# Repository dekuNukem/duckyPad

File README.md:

# duckyPad: Do-It-All Mechanical Macropad

[Get duckyPad](https://dekunukem.github.io/duckyPad-Pro/doc/landing.html) | [Official Discord](https://discord.gg/4sJCBx5) | [Getting Started](getting_started.md) | [Table of Contents](#table-of-contents)

----

duckyPad is a 15-key **mechanical macropad** for power users who demand **advanced macro scripting and customisation** beyond the shackles of QMK/VIA.

Using a [turing-complete scripting language](https://dekunukem.github.io/duckyPad-Pro/doc/duckyscript_info.html), you can automate **any keyboard/mouse input** you want, from **simple combos** to **full-blown programs**.

## Get One

duckyPad was successfully [funded on Kickstarter](https://www.kickstarter.com/projects/dekunukem/duckypad-do-it-all-mechanical-macropad) thanks to the [amazing backers!](kickstarter_backers.md)

* Now Available [on my Tindie Store](https://www.tindie.com/products/dekunukem/duckypad-do-it-all-mechanical-macropad/)

## Highlights

duckyPad has all the basics:

* **Hot-swap**
* Per-key RGB
* Fully **open-source**

But also unique features **not seen anywhere else**:

* Custom **[duckyScript](https://dekunukem.github.io/duckyPad-Pro/doc/duckyscript_info.html)** engine, **NOT QMK/VIA**.
* **Longer and more complex** macros
* **OLED** screen
* **32 profiles** of 15 keys, 480 macros total.
* [Automatic profile switching](https://github.com/dekuNukem/duckyPad-profile-autoswitcher) based on active window.
* microSD storage, move between devices with ease.
* No proprietary drivers, works out-of-box.

## duckyScript vs QMK/VIA

duckyPad uses **duckyScript**, originally designed for [USB Rubber Ducky](https://shop.hak5.org/products/usb-rubber-ducky-deluxe).

Compared to QMK/VIA, you get:

* **Much Longer Macros**
	* [Entire Bee Movie](resources/beemovie.txt) in one macro? Yes please!
	* Up to 480 macros

* **Turing-Complete Scripting**
	* Variables, conditions, loops, functions, and more.
	* Executed on [32-bit Bytecode VM](https://duckypad.github.io/DuckStack/)
	* With **Scratch** and **Non-volatile Memory**

* **Advanced Interactions**
	* Reading Buttons
	* Print to OLED screen
	* Change RGB Color

* **SD Card Storage**
	* Fast Configuration / Backup / Deployment
	* No sketchy drivers or apps
	* No recompiling

While QMK/VIA are great for regular keyboards, they are rather limited at input automations.

duckyScript is a no-brainer for **power users** with more demanding scripting needs.

## 🆕 duckyPad Pro

duckyPad Pro is an updated model with:

* Rotary Encoders
* More Keys
* Bluetooth
* Bigger Display
* More Script Storage
* Expansion Module

👉👉👉 [Purchase Link](https://www.tindie.com/products/37399/) | [More Info](https://dekunukem.github.io/duckyPad-Pro/)

## Discord Community

Feel free to join our [Official Discord](https://discord.gg/4sJCBx5) for discussions, questions, sharing scripts, and latest updates!

## How It Works / Showcase

* Create up to **32 profiles**, one for each application.

* Assign up to **15 keys** per profile

* Names are shown on OLED screen

* Write a **duckyScript** for each key

### Easy Start

* **duckyScript** is a language for automating inputs

	* At simplest, you just tell it **what key to press!**

* Such as **key combos** of your favorite app

`CTRL a` , `CTRL +`, etc.

### Up a Notch

* Once familiar, you can write **longer multi-line macros** to further speed up everyday task.

* Such as **filling forms** and typing **boilerplate text** with one keypress.

```
STRING Michael Scott
TAB
STRING United States
ENTER
STRING 5705550100
TAB
STRING michael.scott@dundermifflin.com
TAB
```

Or a simple mouse jiggler:

```
WHILE TRUE
	MOUSE_MOVE $_RANDOM_INT $_RANDOM_INT
	DELAY 100
END_WHILE
```

### Full Potential

* Going all-out, duckyScript is a **Turing-Complete** **general-purpose** language.
* You can use it to:
	* Read Buttons
	* Write to OLED screen
	* Change RGB colors
	* Perform operations with **32-bit variables**, **conditions**, **loops**, **function call**s, and more!
* Write ultra-specific macros for your exact needs

```
RGB_SET 1 128 0 255

OLED_PRINT You are in a maze
OLED_PRINT of twisty little passages

VAR choice = _READKEY

IF choice == 1
    OLED_CURSOR 0 10
    OLED_PRINT It is a dead end.
    OLED_PRINT Something moves
    OLED_PRINT behind you.
END_IF
```

### Hackerman

* Of course, by automating HID inputs, you can take over an entire computer with the push of a button!

* This is known as [BadUSB attack](https://arstechnica.com/information-technology/2014/07/this-thumbdrive-hacks-computers-badusb-exploit-makes-devices-turn-evil/), and was the original purpose of [USB Rubber Ducky](https://shop.hak5.org/products/usb-rubber-ducky-deluxe).

---------

### Nothing Like It

* From **simple shortcuts** to **full-blown programs**, duckyScript can easily achieve what was impossible on QMK/VIA.

* Each macro can contain over **50,000 characters**

* Store **480 macros** in total

* Executed on custom [virtual stack machine](https://duckypad.github.io/DuckStack/)

## Features

### Switches & Keycaps

duckyPad is compatible with Cherry MX-style mechanical switches (3 or 5-pin).

By default, duckyPad comes with blank translucent ABS R4 keycaps:

You can use your own as well.

### Hot-swap Sockets

duckyPad supports hot-swapping with Kailh sockets.

You can install/remove the switches by hand, **`no soldering needed`**.

### Per-key RGB backlight

Each key on duckyPad has its own RGB backlight. User-configurable colour & brightness.

### OLED screen

duckyPad has an OLED screen. It displays current **`profile and key names`**, so you know what each key does at a glance.

* 128x128
* 1.3 inch
* High contrast with true black
* Burn-in Prevention

### Companion App

[Use the open-source configurator](https://github.com/duckyPad/duckyPad-Configurator) to set up your duckyPad Pro.

* Windows | Mac | Linux
* No account / subscription needed
* No data collection / telemetry

## Profile Auto-switching

* [Automatically jump to the appropriate profile](https://github.com/dekuNukem/duckyPad-profile-autoswitcher)
* Based on **current active window**

### USB-C and Device Compatibility

duckyPad uses USB-C connector for maximum device compatibility.

You can use duckyPad out-of-box on pretty much anything that supports USB keyboards, **`no driver needed`**. Examples include:

* PC
* Mac
* Linux
* Raspberry Pi
* iPhone / iPad
* Android phones and tablets
* Chromebooks
* Game consoles

duckyPad’s firmware can also be [easily updated via USB-C](firmware_updates_and_version_history.md) for new features and bug fixes.

### Keyboard Layouts

duckyPad supports multiple keyboard layouts:

* English (US)
* English (UK)
* French
* Belgium
* German
* Dvorak
* ...and more [user-created](keymap_instructions.md) layouts!

### Dimensions

[Click me](pcb/plates) for vector files of front and back plates.

[Click me](resources/pics/dimensions.png) for dimensions drawings.

## Getting Started

Please see [the instruction manual](./getting_started.md) on how to use your duckyPad.

## I Want One!

duckyPad is [now available on Tindie.](https://www.tindie.com/products/21984)

Also consider [joining our discord](https://discord.gg/4sJCBx5) for latest updates and discussions.

## Table of Contents

[Main page](README.md)

[Getting Started Guide](getting_started.md)

[Kit Assembly Guide](kit_assembly_guide.md)

[Using duckyScript](https://dekunukem.github.io/duckyPad-Pro/doc/duckyscript_info.html)

[Common issues / Troubleshooting](troubleshooting.md)

[Firmware Updates and Version History](firmware_updates_and_version_history.md)

[Make Your Own Keymap](./keymap_instructions.md)

[Build a duckyPad Yourself](build_it_yourself.md)

[Kickstarter Backer Acknowledgments](kickstarter_backers.md)

## Questions or Comments?

Please feel free to [open an issue](https://github.com/dekuNukem/duckypad/issues), ask in the [official duckyPad discord](https://discord.gg/4sJCBx5), DM me on discord `dekuNukem#6998`, or email `dekuNukem`@`gmail`.`com` for inquires.

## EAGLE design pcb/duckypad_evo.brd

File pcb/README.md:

Currently no pcb files are available.

The used pins can be seen from the lul.ioc files when the device is handsoldered.

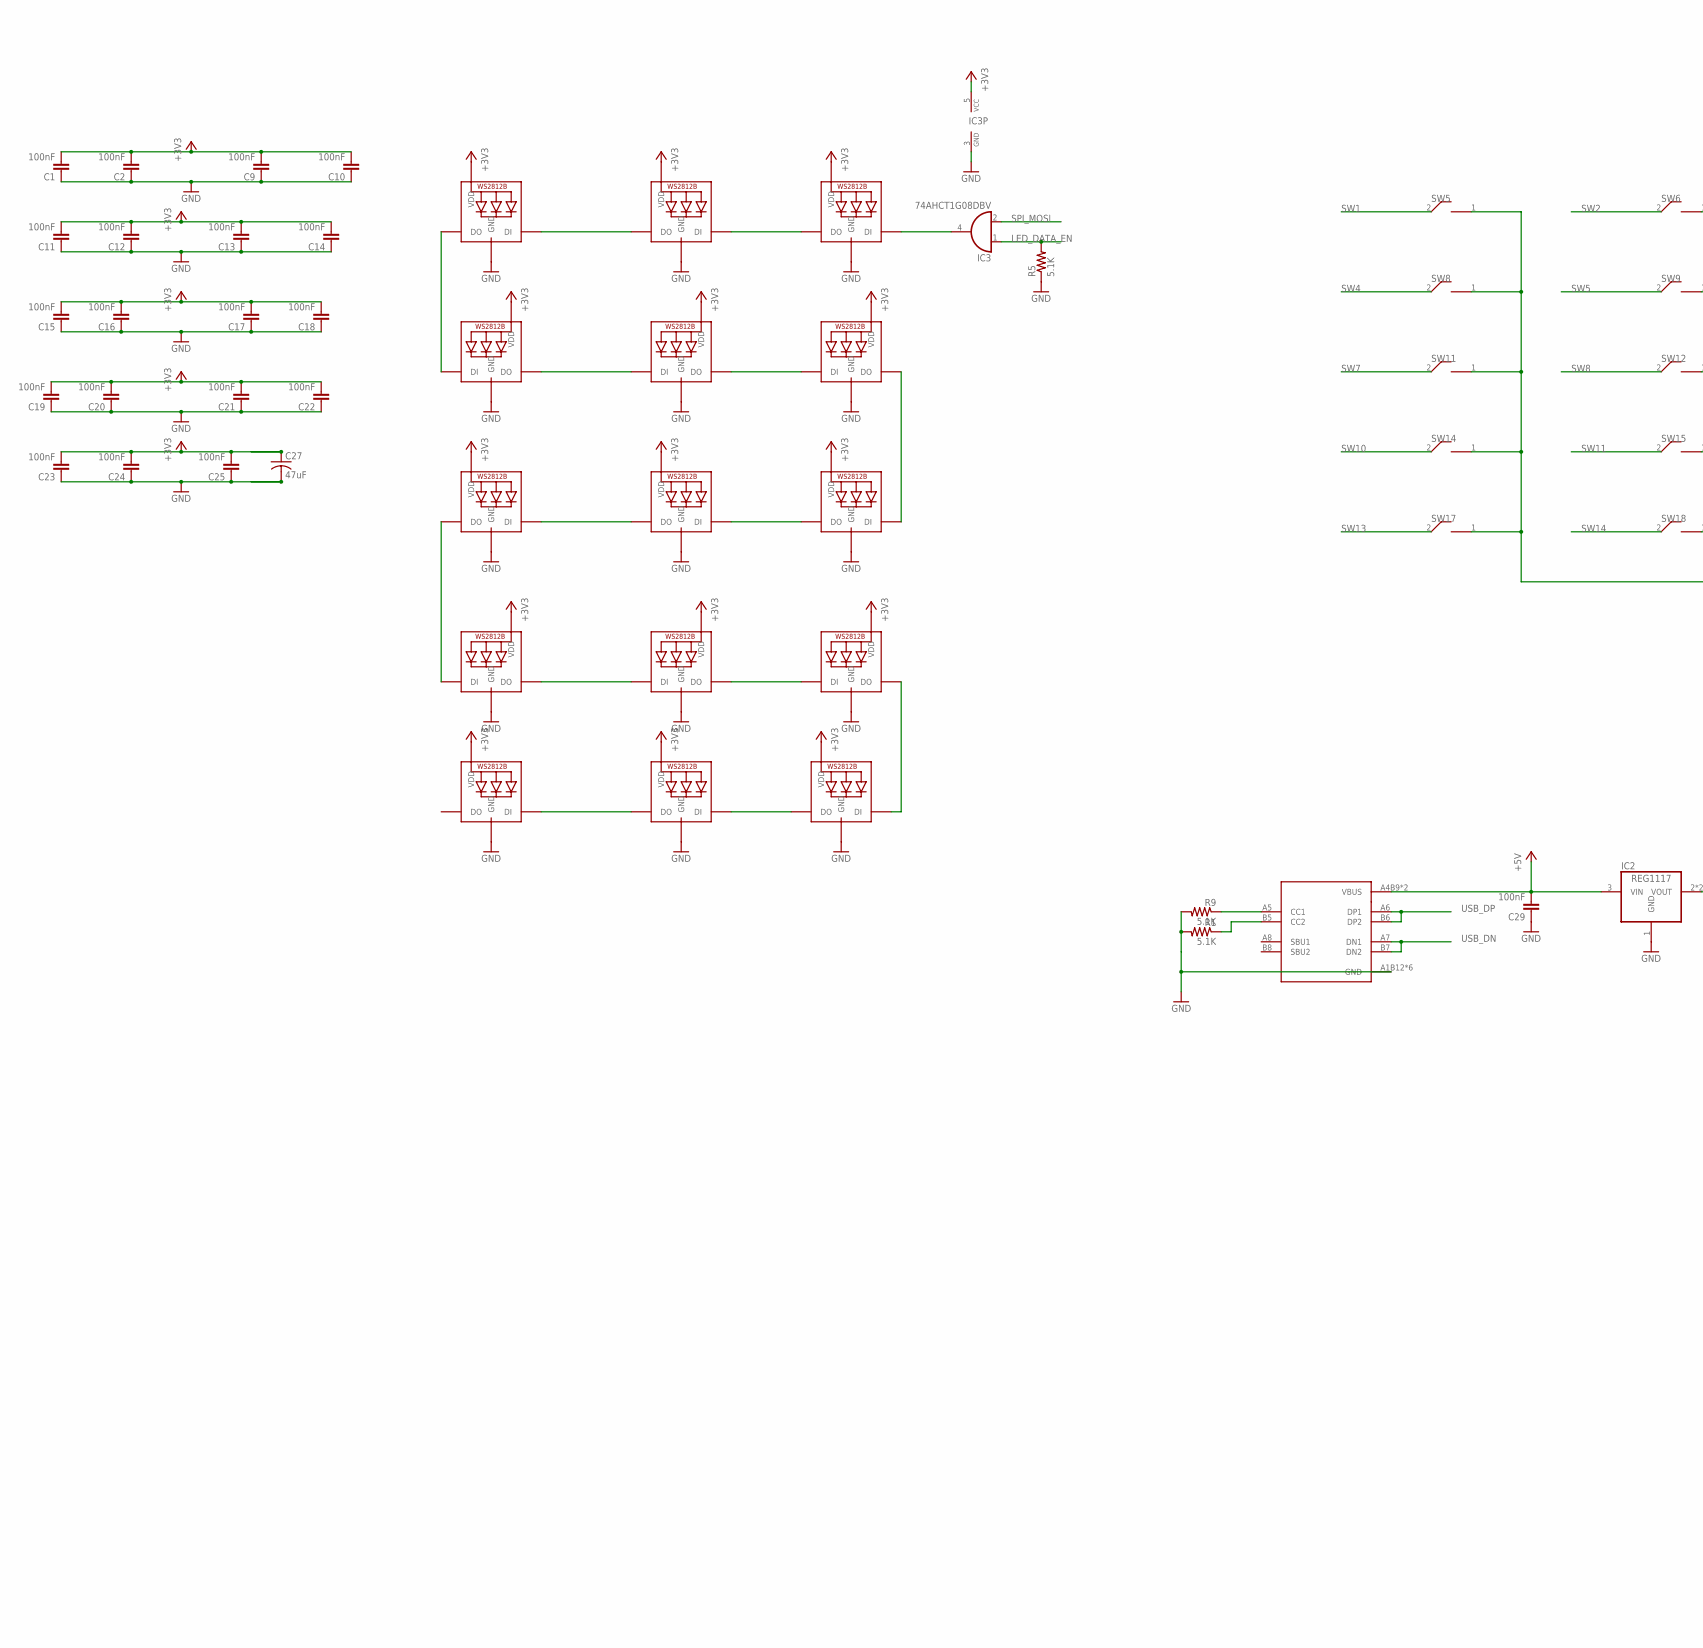
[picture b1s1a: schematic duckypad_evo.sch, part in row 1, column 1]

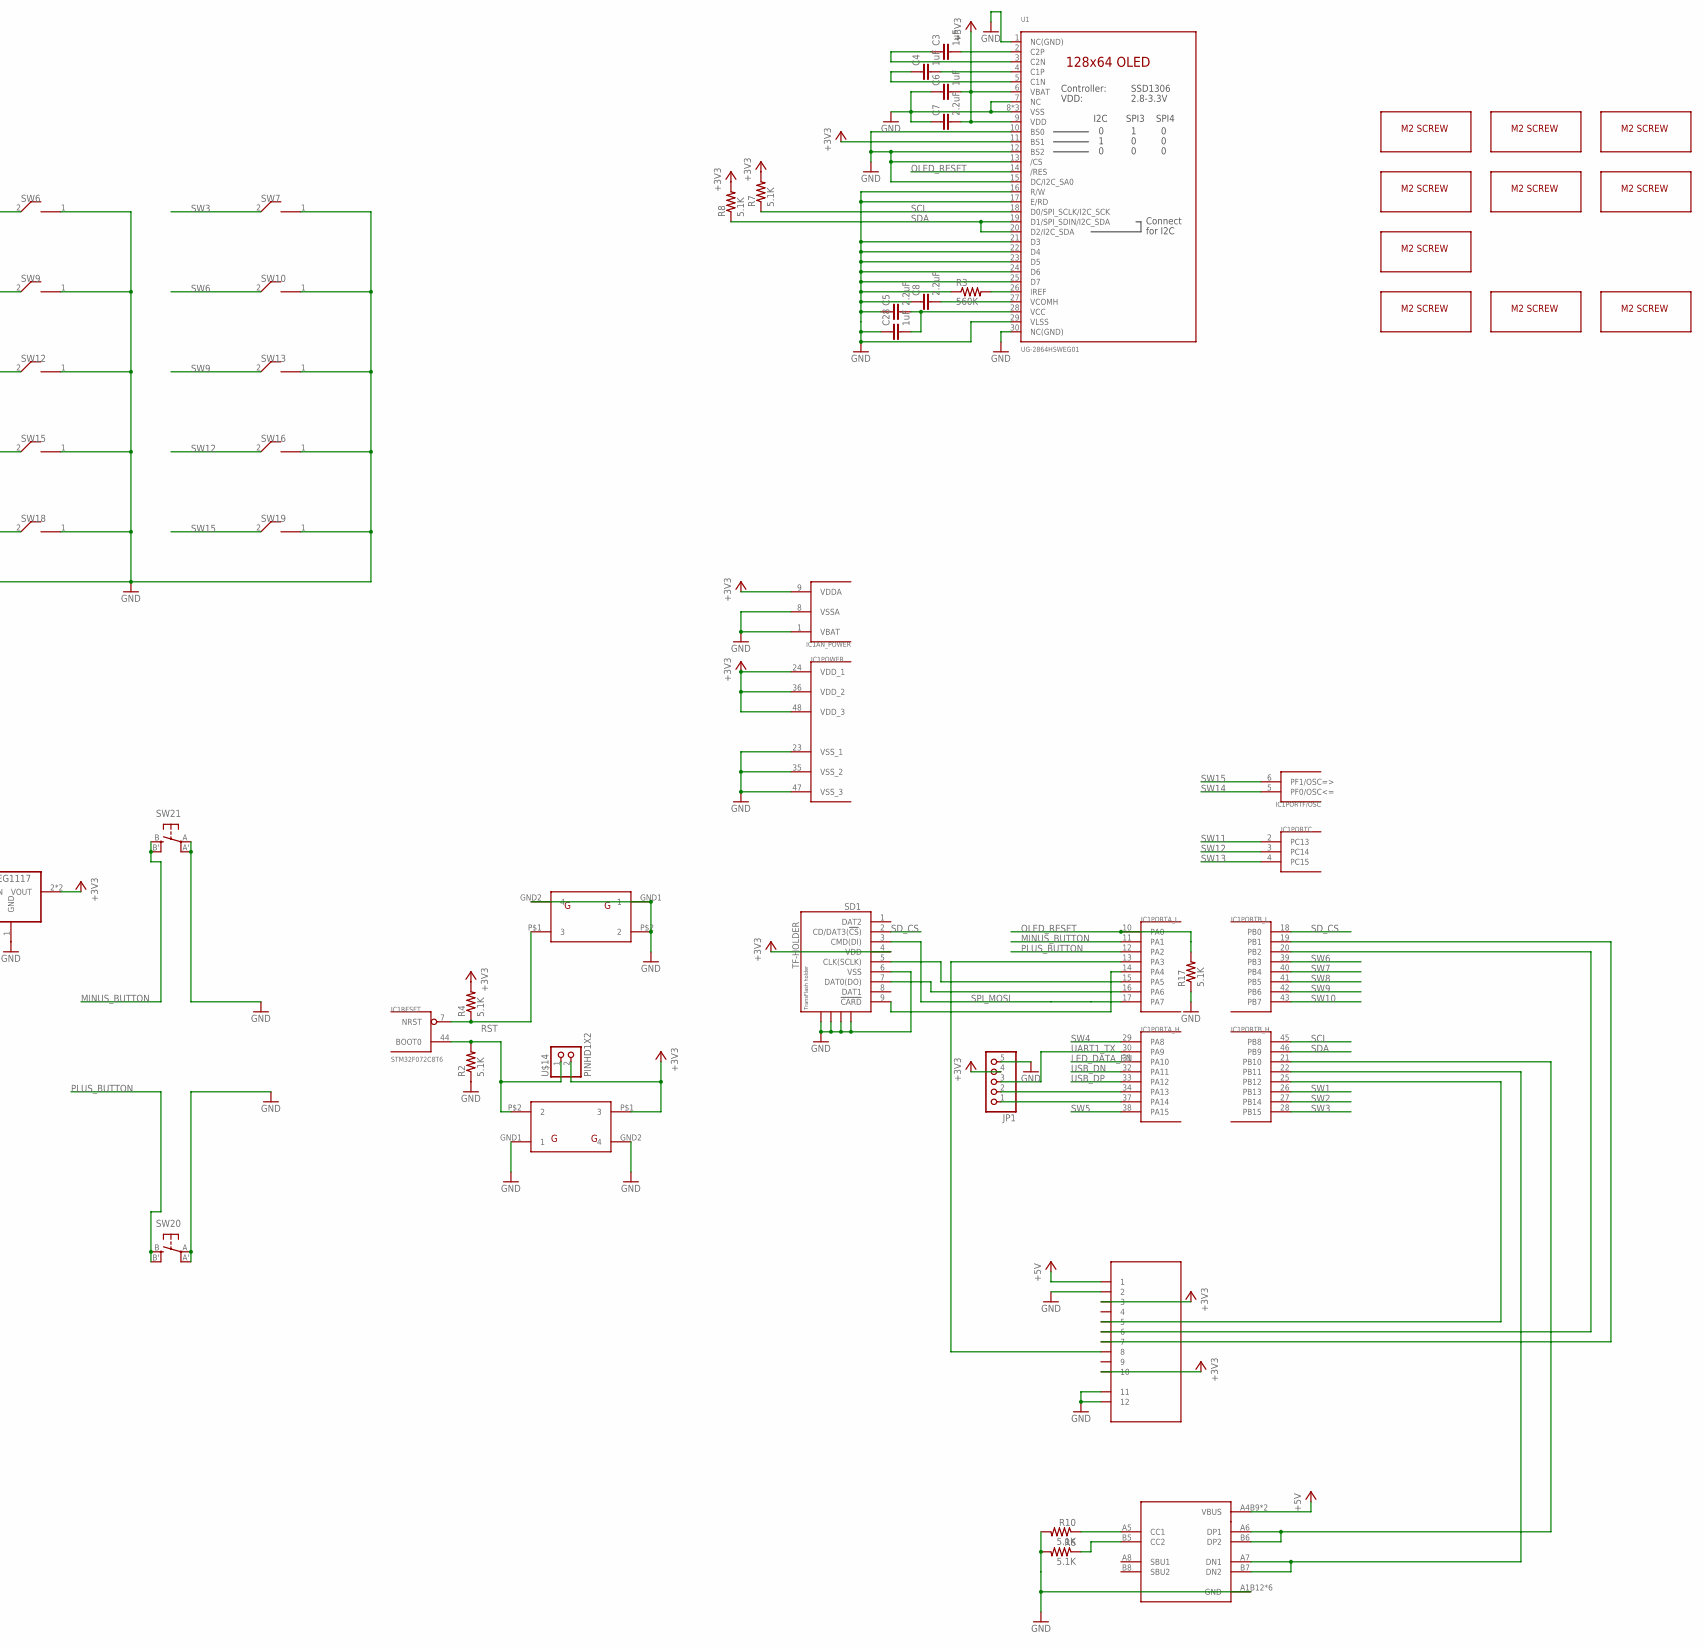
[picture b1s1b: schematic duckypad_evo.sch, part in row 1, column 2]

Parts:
C1, C2, C9, C10, C11, C12, C13, C14, C15, C16, C17, C18, C19, C20, C21, C22, C23, C24, C25, C29: 100nF; 0805@1
C3, C4, C6, C28: 1uF; 0805@1
C5, C7, C8: 2.2uF; 0805@1
C27: 47uF; C1210
IC1: STM32F072C8T6; TQFP48
IC2: REG1117; SOT223
IC3: 74AHCT1G08DBV; SOT23-5
JP1: PINHD-1X5; 1X05
LED1, LED2, LED3, LED4, LED5, LED6, LED7, LED8, LED9, LED10, LED11, LED12, LED13, LED14, LED15: WS2812B; REVERSE_MNT
R1, R2, R4, R5, R6, R7, R8, R9, R10, R17: 5.1K; 0805
R3: 560K; 0805
SD1: TF-HOLDER; TF-PULL
SH1: SH10P; DUCKYPAD_SM12B-SSR-H-TB
SW3, SW4: 3POS_SLIDE_SWITCH_324_SW; SIDEPUSH
SW5, SW6, SW7, SW8, SW9, SW10, SW11, SW12, SW13, SW14, SW15, SW16, SW17, SW18, SW19: KAILH_SWITCH_SOCKET_KAILH_SWITCH_SOCKET; KAILH_SWITCH_SOCKET_SWITCH_SOCKET
SW20, SW21: SPST_TACT-EVQQ2; EVQ-Q2
U1: UG-2864HSWEG01; LUL_UG-2864HSWEG01_1.3_WRAPAROUND
U2, U3: USBC_16P; USBC_16P_FOOT
U$7, U$8, U$9, U$10, U$11, U$12, U$13, U$15, U$16, U$23: M2_SCREW_DEV; M2_SCREW_FOOT
U$14: PINHD1X2; 1X02

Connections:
+3V3: C1.2, C2.2, C6.2, C7.2, C9.2, C10.2, C11.2, C12.2, C13.2, C14.2, C15.2, C16.2, C17.2, C18.2, C19.2, C20.2, C21.2, C22.2, C23.2, C24.2, C25.2, C27.1, IC1.9 (VDDA), IC1.24 (VDD_1), IC1.36 (VDD_2), IC1.48 (VDD_3), IC2.2 (VOUT), IC2.4 (VOUT), IC3.5 (VCC), JP1.4, LED1.VDD, LED2.VDD, LED3.VDD, LED4.VDD, LED5.VDD, LED6.VDD, LED7.VDD, LED8.VDD, LED9.VDD, LED10.VDD, LED11.VDD, LED12.VDD, LED13.VDD, LED14.VDD, LED15.VDD, R4.2, R7.2, R8.2, SD1.4 (VDD), SH1.3, SH1.10, SW4.P$1 (3), U1.6 (VBAT), U1.9 (VDD), U1.11 (BS1), U$14.2
+5V: C29.2, IC2.3 (VIN), SH1.1, U2.A4B9 (VBUS), U2.B4A9 (VBUS), U3.A4B9 (VBUS), U3.B4A9 (VBUS)
BUTTON_DEBUG: IC1.44 (BOOT0), R2.2, SW4.P$2 (2), U$14.1
GND: C1.1, C2.1, C5.1, C6.1, C7.1, C8.1, C9.1, C10.1, C11.1, C12.1, C13.1, C14.1, C15.1, C16.1, C17.1, C18.1, C19.1, C20.1, C21.1, C22.1, C23.1, C24.1, C25.1, C27.2, C28.1, C29.1, IC1.1 (VBAT), IC1.8 (VSSA), IC1.23 (VSS_1), IC1.35 (VSS_2), IC1.47 (VSS_3), IC2.1 (GND), IC3.3 (GND), JP1.5, LED1.GND, LED2.GND, LED3.GND, LED4.GND, LED5.GND, LED6.GND, LED7.GND, LED8.GND, LED9.GND, LED10.GND, LED11.GND, LED12.GND, LED13.GND, LED14.GND, LED15.GND, R1.2, R2.1, R3.1, R5.1, R6.2, R9.2, R10.2, R17.1, SD1.6 (VSS), SD1.S1, SD1.S2, SD1.S3, SD1.S4, SH1.2, SH1.FIT@1 (11), SH1.FIT@2 (12), SW3.GND1 (1), SW3.GND2 (4), SW3.P$2 (2), SW4.GND1 (1), SW4.GND2 (4), SW5.1 (2), SW6.1 (2), SW7.1 (2), SW8.1 (2), SW9.1 (2), SW10.1 (2), SW11.1 (2), SW12.1 (2), SW13.1 (2), SW14.1 (2), SW15.1 (2), SW16.1 (2), SW17.1 (2), SW18.1 (2), SW19.1 (2), SW20.A, SW20.A' (P1), SW21.A, SW21.A' (P1), U1.1 (NC(GND)), U1.7 (NC), U1.8 (VSS), U1.10 (BS0), U1.12 (BS2), U1.13 (/CS), U1.15 (DC/I2C_SA0), U1.16 (R/W), U1.17 (E/RD), U1.21 (D3), U1.22 (D4), U1.23 (D5), U1.24 (D6), U1.25 (D7), U1.29 (VLSS), U1.30 (NC(GND)), U1.31 (VSS), U1.32 (VSS), U2.A1B12 (GND), U2.B11A12 (GND), U2.P$13 (GND), U2.P$14 (GND), U2.P$15 (GND), U2.P$16 (GND), U3.A1B12 (GND), U3.B11A12 (GND), U3.P$13 (GND), U3.P$14 (GND), U3.P$15 (GND), U3.P$16 (GND)
LED_DATA_EN: IC1.31 (PA10), IC3.1 (I0), R5.2
MINUS_BUTTON: IC1.11 (PA1), SW21.B (S), SW21.B' (S1)
unnamed: R6.1, U3.B5 (CC2)
unnamed: IC1.20 (PB2), SH1.6
unnamed: R3.2, U1.26 (IREF)
unnamed: C3.2, U1.2 (C2P)
unnamed: C3.1, U1.3 (C2N)
unnamed: C4.2, U1.4 (C1P)
unnamed: C4.1, U1.5 (C1N)
unnamed: IC1.15 (PA5), SD1.5 (CLK(SCLK))
unnamed: LED2.DIN (DI), LED3.DOUT (DO)
unnamed: IC1.16 (PA6), SD1.7 (DAT0(DO))
unnamed: C5.2, C28.2, U1.28 (VCC)
unnamed: C8.2, U1.27 (VCOMH)
unnamed: IC1.19 (PB1), SH1.7
unnamed: IC1.14 (PA4), SD1.9 (!CARD)
unnamed: LED1.DIN (DI), LED2.DOUT (DO)
unnamed: IC1.22 (PB11), U3.A7 (DN1), U3.B7 (DN2)
unnamed: LED1.DOUT (DO), LED4.DIN (DI)
unnamed: LED4.DOUT (DO), LED5.DIN (DI)
unnamed: LED5.DOUT (DO), LED6.DIN (DI)
unnamed: LED6.DOUT (DO), LED9.DIN (DI)
unnamed: LED8.DIN (DI), LED9.DOUT (DO)
unnamed: LED7.DIN (DI), LED8.DOUT (DO)
unnamed: LED7.DOUT (DO), LED10.DIN (DI)
unnamed: LED10.DOUT (DO), LED11.DIN (DI)
unnamed: LED11.DOUT (DO), LED12.DIN (DI)
unnamed: LED12.DOUT (DO), LED15.DIN (DI)
unnamed: LED14.DIN (DI), LED15.DOUT (DO)
unnamed: LED13.DIN (DI), LED14.DOUT (DO)
unnamed: IC3.4 (O), LED3.DIN (DI)
unnamed: IC1.21 (PB10), U3.A6 (DP1), U3.B6 (DP2)
unnamed: R1.1, U2.B5 (CC2)
unnamed: IC1.37 (PA14), JP1.1
unnamed: R9.1, U2.A5 (CC1)
unnamed: IC1.34 (PA13), JP1.2
unnamed: IC1.25 (PB12), SH1.5
unnamed: R10.1, U3.A5 (CC1)
unnamed: IC1.13 (PA3), SH1.8
OLED_RESET: IC1.10 (PA0), R17.2, U1.14 (/RES)
PLUS_BUTTON: IC1.12 (PA2), SW20.B (S), SW20.B' (S1)
RST: IC1.7 (NRST), R4.1, SW3.P$1 (3)
SCL: IC1.45 (PB8), R7.1, U1.18 (D0/SPI_SCLK/I2C_SCK)
SDA: IC1.46 (PB9), R8.1, U1.19 (D1/SPI_SDIN/I2C_SDA), U1.20 (D2/I2C_SDA)
SD_CS: IC1.18 (PB0), SD1.2 (CD/DAT3(!CS!))
SPI_MOSI: IC1.17 (PA7), IC3.2 (I1), SD1.3 (CMD(DI))
SW1: IC1.26 (PB13), SW5.2 (1)
SW2: IC1.27 (PB14), SW6.2 (1)
SW3: IC1.28 (PB15), SW7.2 (1)
SW4: IC1.29 (PA8), SW8.2 (1)
SW5: IC1.38 (PA15), SW9.2 (1)
SW6: IC1.39 (PB3), SW10.2 (1)
SW7: IC1.40 (PB4), SW11.2 (1)
SW8: IC1.41 (PB5), SW12.2 (1)
SW9: IC1.42 (PB6), SW13.2 (1)
SW10: IC1.43 (PB7), SW14.2 (1)
SW11: IC1.2 (PC13), SW15.2 (1)
SW12: IC1.3 (PC14), SW16.2 (1)
SW13: IC1.4 (PC15), SW17.2 (1)
SW14: IC1.5 (PF0/OSC<=), SW18.2 (1)
SW15: IC1.6 (PF1/OSC=>), SW19.2 (1)
UART1_TX: IC1.30 (PA9), JP1.3
USB_DN: IC1.32 (PA11), U2.A7 (DN1), U2.B7 (DN2)
USB_DP: IC1.33 (PA12), U2.A6 (DP1), U2.B6 (DP2)

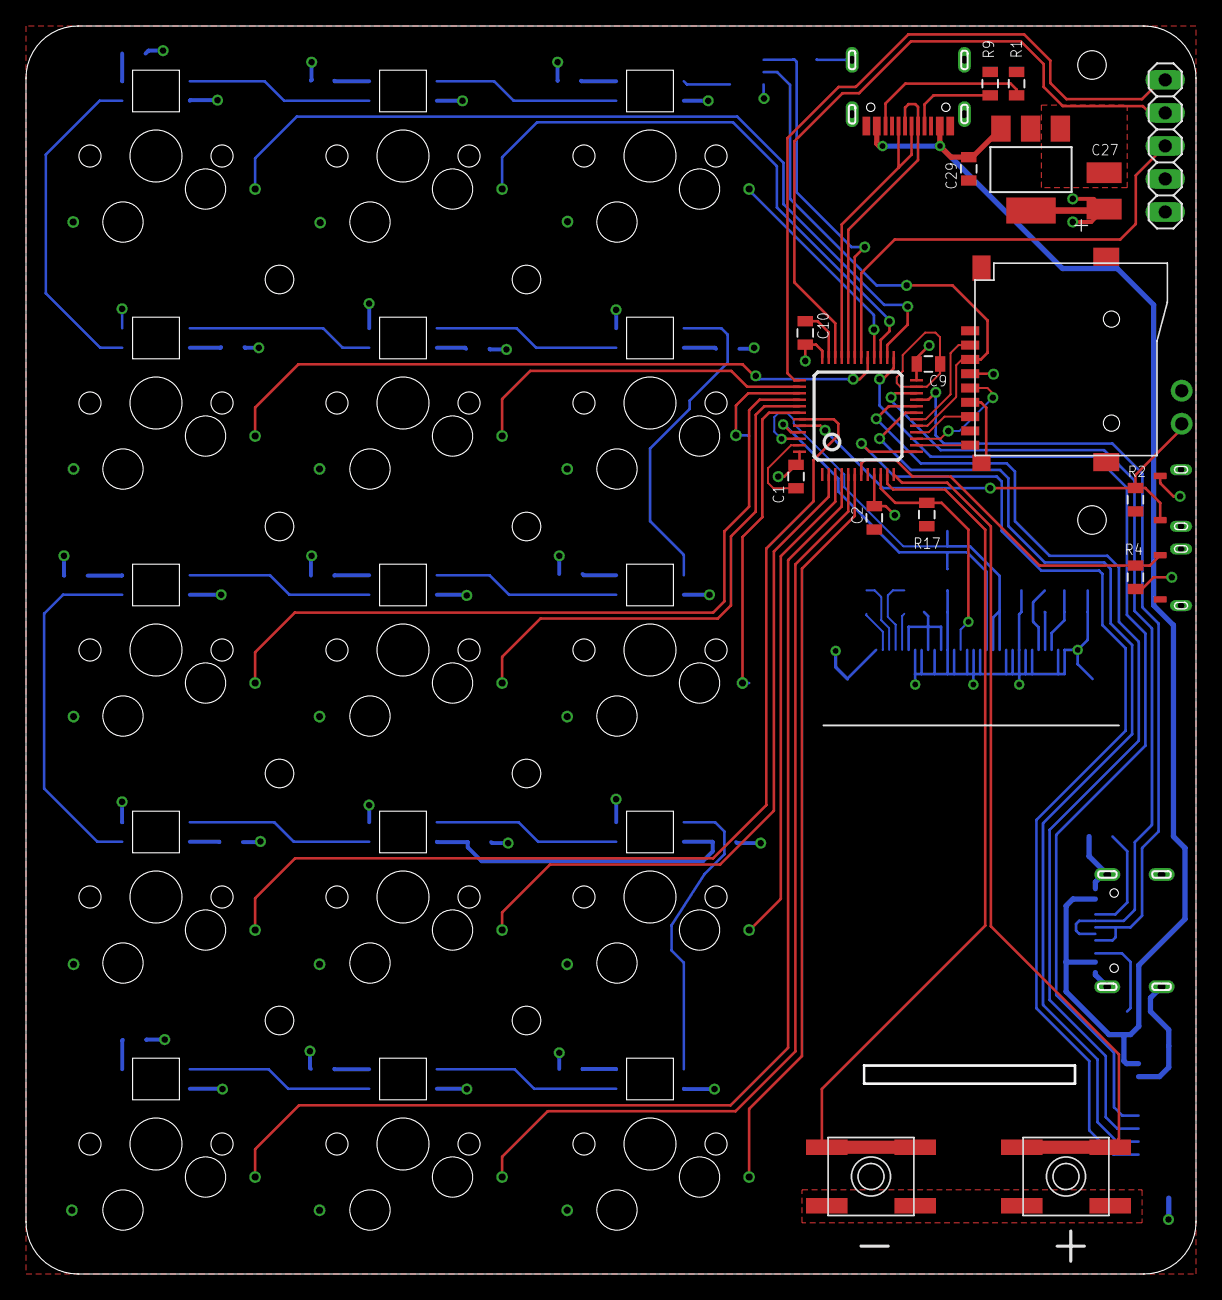
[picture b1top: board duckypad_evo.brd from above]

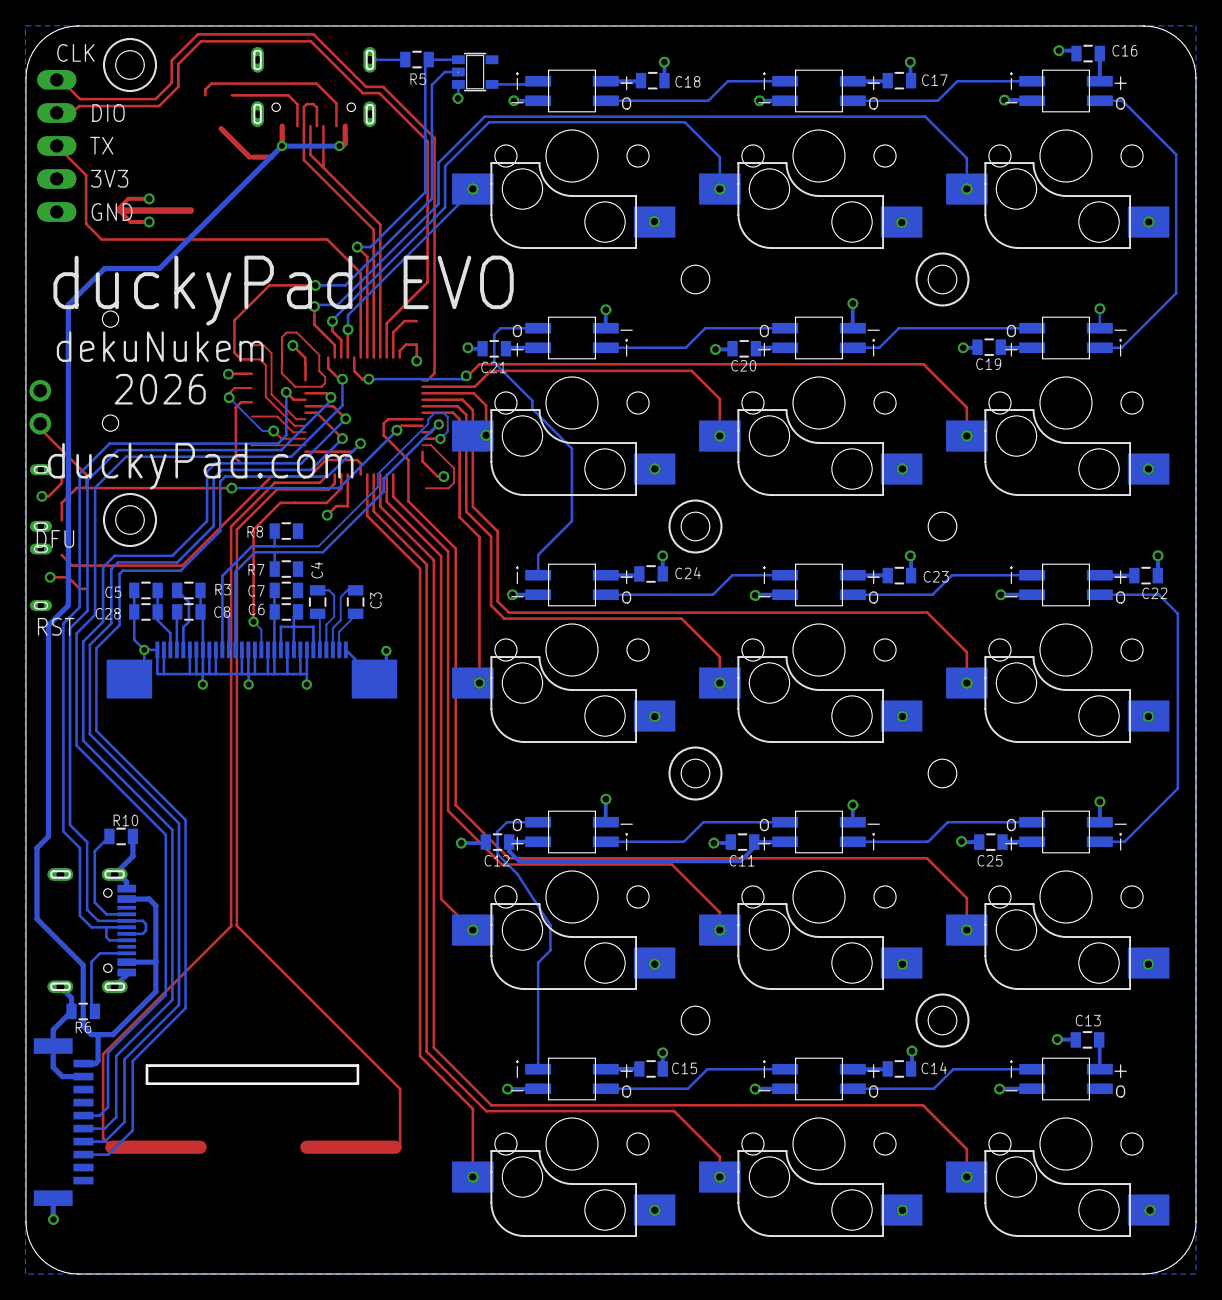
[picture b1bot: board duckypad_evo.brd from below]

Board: 2 copper layers, 90.0 x 96.0 mm, 93 parts (31 on the bottom side), 68 nets.

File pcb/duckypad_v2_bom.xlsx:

Qty | Value | Device | Parts
4 | 1uF | 0805 Capacitor | C3, C4, C6, C28
3 | 2.2uF | 0805 Capacitor | C5, C7, C8
4 | 5.1K | 0805 Resistor | R1, R7, R8, R9
4 | 10K | 0805 Resistor | R2, R4, R5, R17
1 | 47uF | 1210 Tantalum Capacitor | C27
1 |  | 74LVC1G08 | IC3
20 | 100nF | 0805 Capacitor | C1, C2, C9, C10, C11, C12, C13, C14, C15, C16, C17, C18, C19, C20, C21, C22, C2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
4 |  | Tactile Switch | SW1, SW2, SW3, SW4
1 | 560K | 0805 Resistor | R3
15 |  | CherryMX-style Key Switch | S1, S2, S3, S4, S5, S6, S7, S8, S9, S10, S11, S12, S13, S14, S15
1 | 3.3V | 1117 Regulator | IC2
1 |  | STM32F072C8T6 | IC1
1 |  | MicroSD Sard Holder | SD1
1 |  | 30 pin FPC Connecter for OLED, Upper Contact | U1
1 |  | USB-C Connector 16Pin | U2
15 |  | SK6812 RGB LED | LED1, LED2, LED3, LED4, LED5, LED6, LED7, LED8, LED9, LED10, LED11, LED12, LED1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

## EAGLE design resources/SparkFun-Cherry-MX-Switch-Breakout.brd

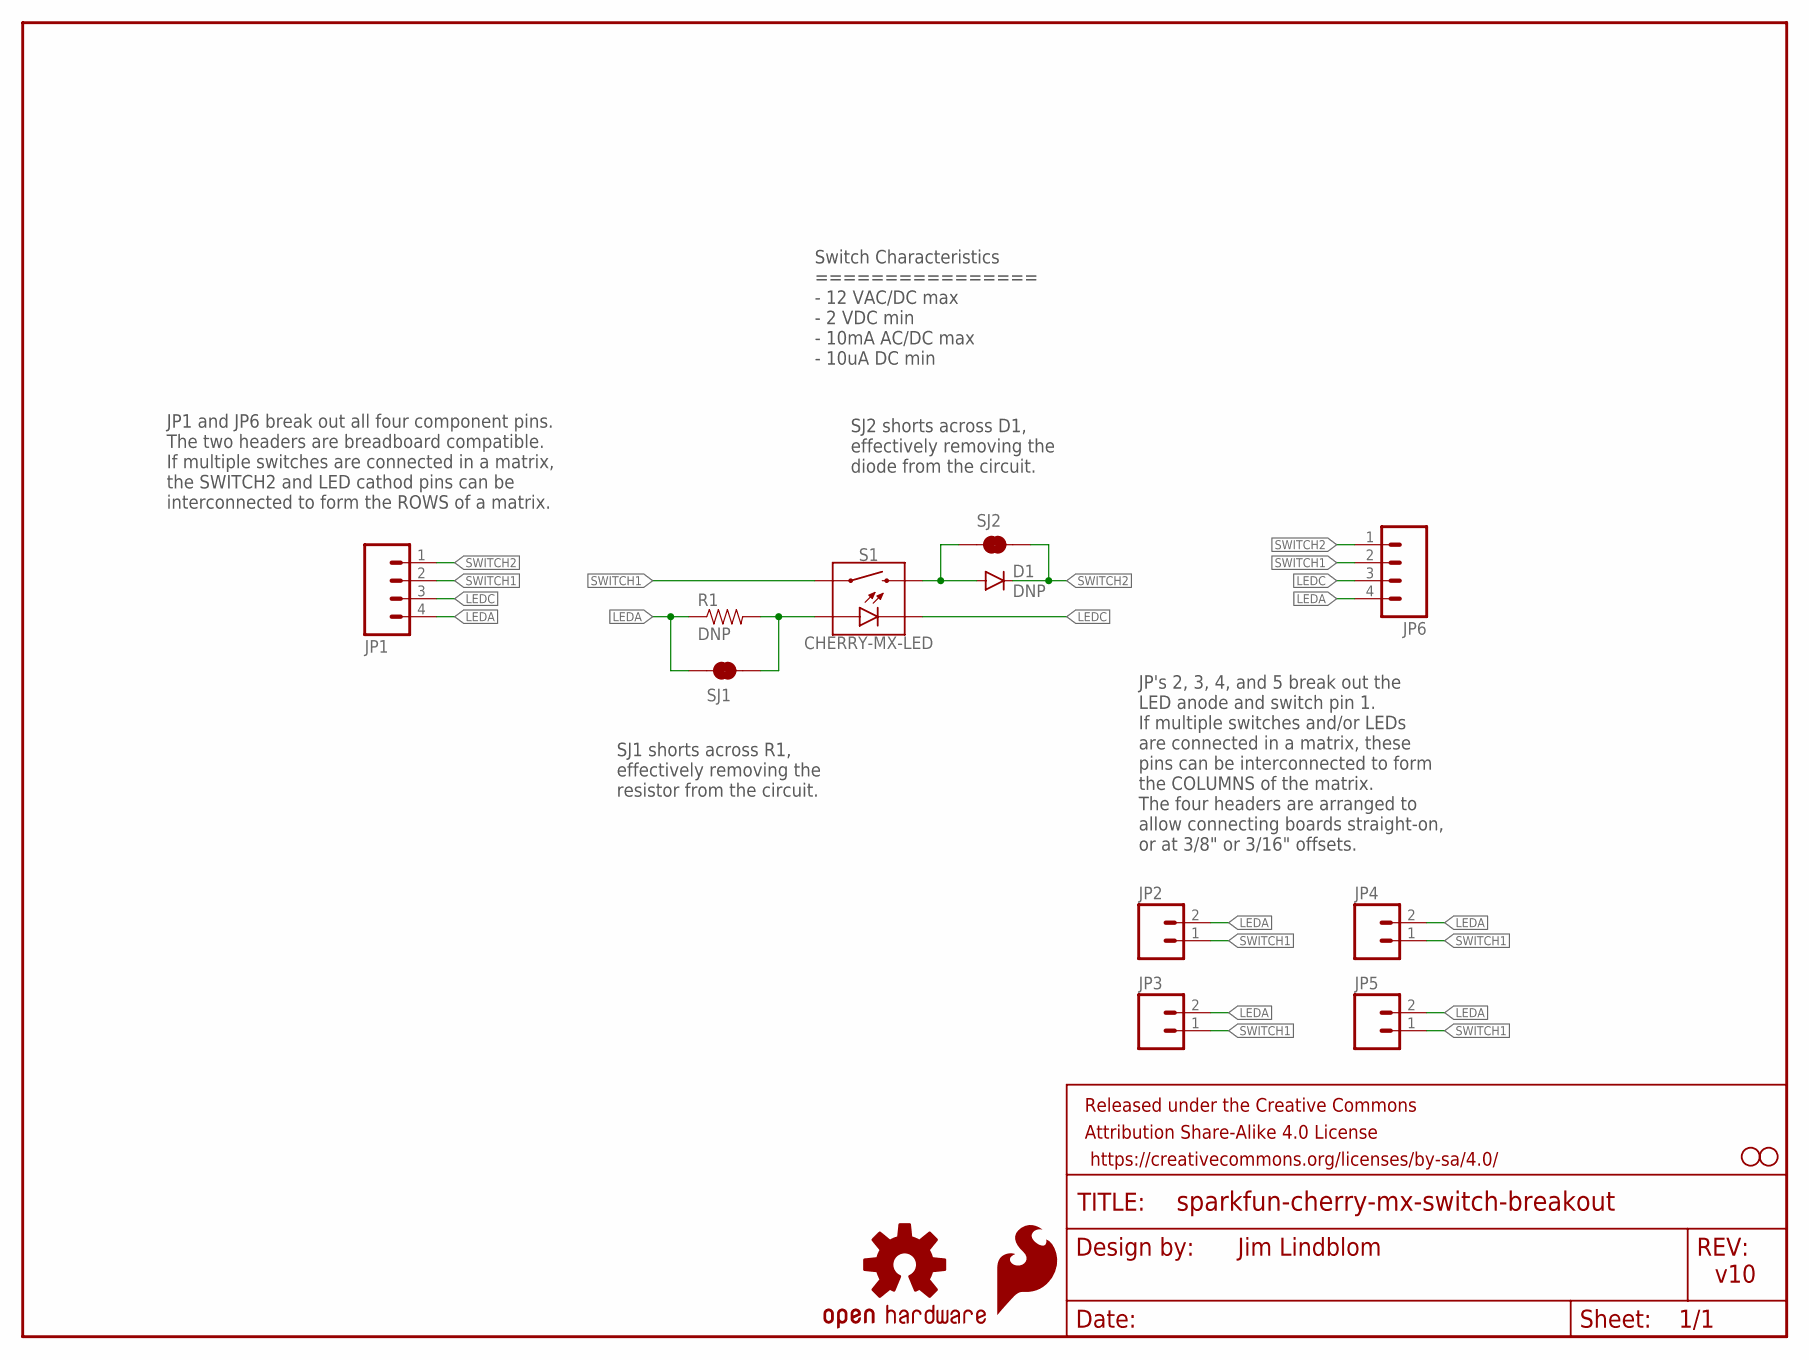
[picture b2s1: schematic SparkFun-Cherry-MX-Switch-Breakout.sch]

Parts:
D1: DNP; DIODE-PTH-0.1
FRAME1: FRAME-LETTER; CREATIVE_COMMONS
JP1, JP6: M04NO_SILK_ALL_ROUND; 1X04_NO_SILK_ALL_ROUND
JP2, JP3, JP4, JP5: M021X02_NO_SILK; 1X02_NO_SILK
LOGO1: OSHW-LOGOS; OSHW-LOGO-S
LOGO2: SFE_LOGO_FLAME.1_INCH; SFE_LOGO_FLAME_.1
R1: DNP; AXIAL-0.1
S1: CHERRY-MX-LED
SJ1, SJ2: JUMPER-PAD-2-NC_BY_TRACENO_SILK; PAD-JUMPER-2-NC_BY_TRACE_NO_SILK
STANDOFF1, STANDOFF2: STAND-OFF2-56; STAND-OFF-2-56

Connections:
LEDA: JP1.4, JP2.2, JP3.2, JP4.2, JP5.2, JP6.4, R1.P$1 (1), SJ1.1
LEDC: JP1.3, JP6.3, S1.K (C)
unnamed: R1.P$2 (2), S1.A, SJ1.2
unnamed: D1.A, S1.S2, SJ2.1
SWITCH1: JP1.2, JP2.1, JP3.1, JP4.1, JP5.1, JP6.2, S1.S1
SWITCH2: D1.C, JP1.1, JP6.1, SJ2.2

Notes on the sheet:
v10
Jim Lindblom
SJ1 shorts across R1, effectively removing the resistor from the circuit.
SJ2 shorts across D1, effectively removing the diode from the circuit.
JP's 2, 3, 4, and 5 break out the LED anode and switch pin 1. If multiple switches and/or LEDs are connected in a matrix, these pins can be interconnected to form the COLUMNS of the matrix. The four headers are arranged to allow connecting boards straight-on, or at 3/8" or 3/16" offsets.
JP1 and JP6 break out all four component pins. The two headers are breadboard compatible. If multiple switches are connected in a matrix, the SWITCH2 and LED cathod pins can be interconnected to form the ROWS of a matrix.
Switch Characteristics ================ - 12 VAC/DC max - 2 VDC min - 10mA AC/DC max - 10uA DC min

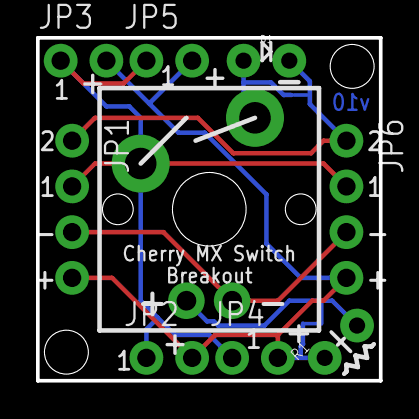
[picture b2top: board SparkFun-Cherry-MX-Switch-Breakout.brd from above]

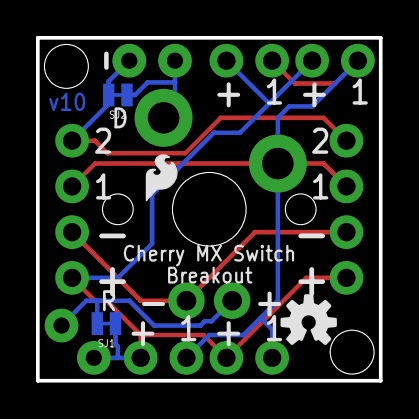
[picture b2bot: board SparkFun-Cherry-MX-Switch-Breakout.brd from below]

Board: 2 copper layers, 19.1 x 19.1 mm, 16 parts (4 on the bottom side), 6 nets.

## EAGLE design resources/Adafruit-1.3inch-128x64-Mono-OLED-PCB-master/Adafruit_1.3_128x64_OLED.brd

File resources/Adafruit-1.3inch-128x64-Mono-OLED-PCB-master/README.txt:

This is the PCB for the Adafruit 128x64 I2C/SPI 1.3" OLED breakout board
Format is EagleCAD schematic and board layout

For more details, check out the product page at

-----> http://www.adafruit.com/products/938

Adafruit invests time and resources providing this open source design, 
please support Adafruit and open-source hardware by purchasing 
products from Adafruit!

Designed by Adafruit Industries.  
Creative Commons Attribution, Share-Alike license, check license.txt for more information
All text above must be included in any redistribution

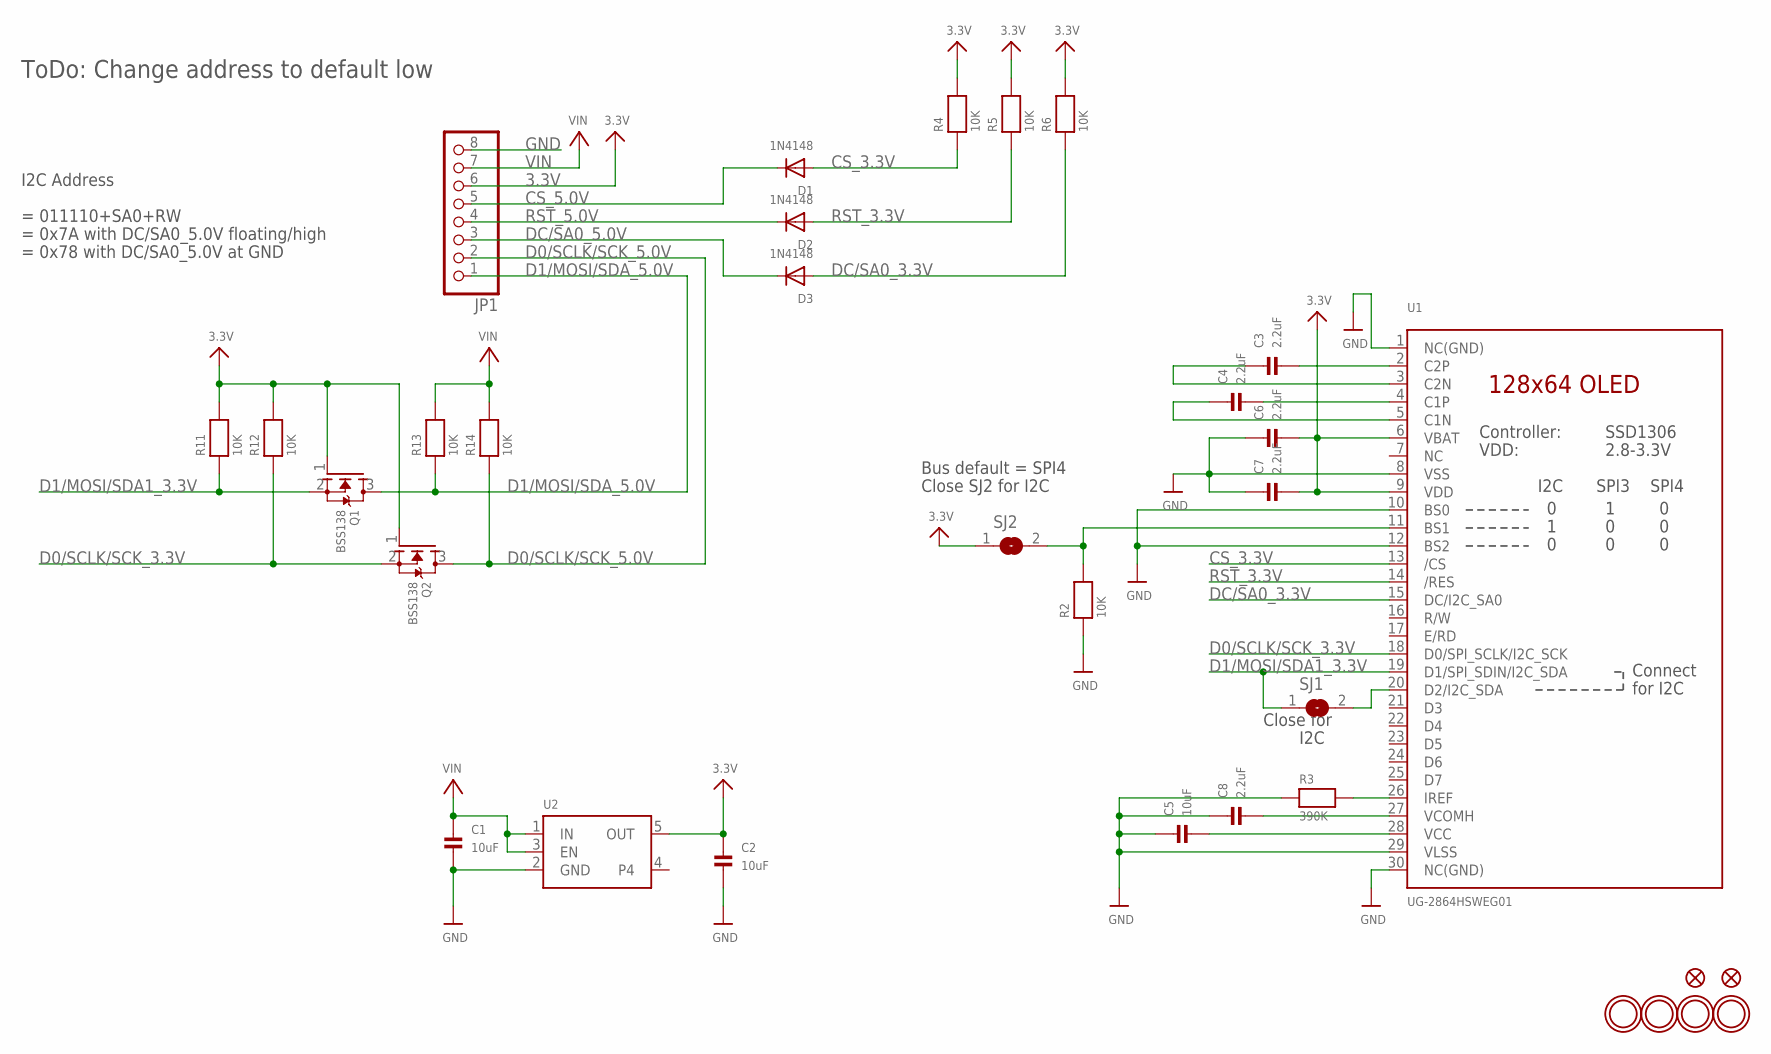
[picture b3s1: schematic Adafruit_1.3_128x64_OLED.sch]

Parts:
C1, C2, C5: 10uF; 0805
C3, C4, C6, C7, C8: 2.2uF; 0805
D1, D2, D3: 1N4148; SOD-323
FID1, FID2: FIDUCIAL""; FIDUCIAL_1MM
JP1: HEADER-1X870MIL; 1X08_ROUND_70
Q1, Q2: BSS138; SOT23-WIDE
R2, R4, R5, R6, R11, R12, R13, R14: 10K; 0805
R3: 390K; 0805
SJ1, SJ2: SOLDERJUMPERREFLOW_NOPASTE; SOLDERJUMPER_REFLOW_NOPASTE
U1: UG-2864HSWEG01; UG-2864HSWEG01_1.3_WRAPAROUND
U2: VREG_SOT23-5; SOT23-5
U$23, U$24, U$25, U$26: MOUNTINGHOLE2.5; MOUNTINGHOLE_2.5_PLATED

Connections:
3.3V: C2.1, C6.2, C7.2, JP1.6, Q1.1 (G), Q2.1 (G), R4.2, R5.2, R6.2, R11.2, R12.2, SJ2.1, U1.6 (VBAT), U1.9 (VDD), U2.5 (OUT)
CS_3.3V: D1.A, R4.1, U1.13 (/CS)
CS_5.0V: D1.C, JP1.5
D0/SCLK/SCK_3.3V: Q2.2 (S), R12.1, U1.18 (D0/SPI_SCLK/I2C_SCK)
D0/SCLK/SCK_5.0V: JP1.2, Q2.3 (D), R14.1
D1/MOSI/SDA1_3.3V: Q1.2 (S), R11.1, SJ1.1, U1.19 (D1/SPI_SDIN/I2C_SDA)
D1/MOSI/SDA_5.0V: JP1.1, Q1.3 (D), R13.1
DC/SA0_3.3V: D3.A, R6.1, U1.15 (DC/I2C_SA0)
DC/SA0_5.0V: D3.C, JP1.3
GND: C1.2, C2.2, C5.1, C6.1, C7.1, C8.1, JP1.8, R2.1, R3.1, U1.1 (NC(GND)), U1.8 (VSS), U1.10 (BS0), U1.12 (BS2), U1.29 (VLSS), U1.30 (NC(GND)), U2.2 (GND)
unnamed: R2.2, SJ2.2, U1.11 (BS1)
unnamed: SJ1.2, U1.20 (D2/I2C_SDA)
unnamed: R3.2, U1.26 (IREF)
unnamed: C3.2, U1.2 (C2P)
unnamed: C3.1, U1.3 (C2N)
unnamed: C4.2, U1.4 (C1P)
unnamed: C4.1, U1.5 (C1N)
unnamed: C5.2, U1.28 (VCC)
unnamed: C8.2, U1.27 (VCOMH)
RST_3.3V: D2.A, R5.1, U1.14 (/RES)
RST_5.0V: D2.C, JP1.4
VIN: C1.1, JP1.7, R13.2, R14.2, U2.1 (IN), U2.3 (EN)

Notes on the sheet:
Bus default = SPI4
Close SJ2 for I2C
= 011110+SA0+RW
= 0x7A with DC/SA0_5.0V floating/high
= 0x78 with DC/SA0_5.0V at GND
I2C Address
ToDo: Change address to default low
Close for
I2C

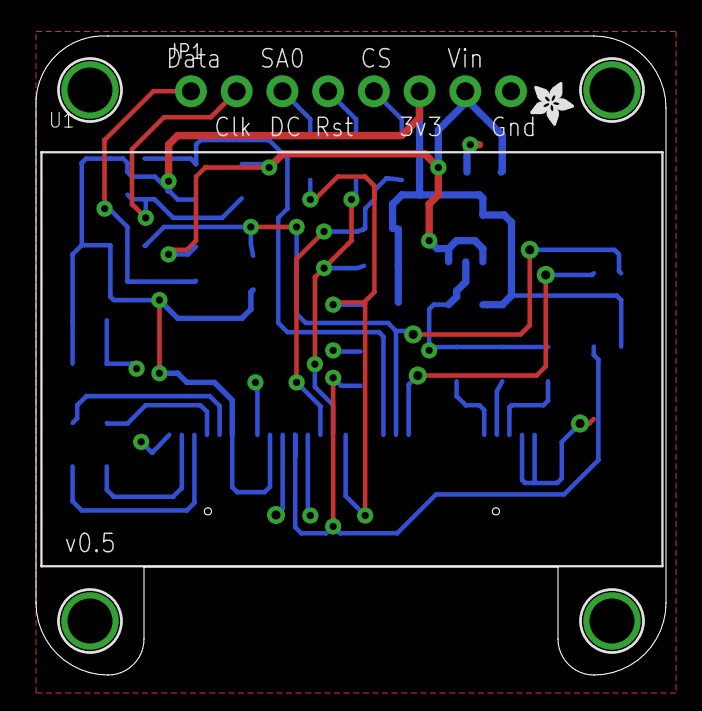
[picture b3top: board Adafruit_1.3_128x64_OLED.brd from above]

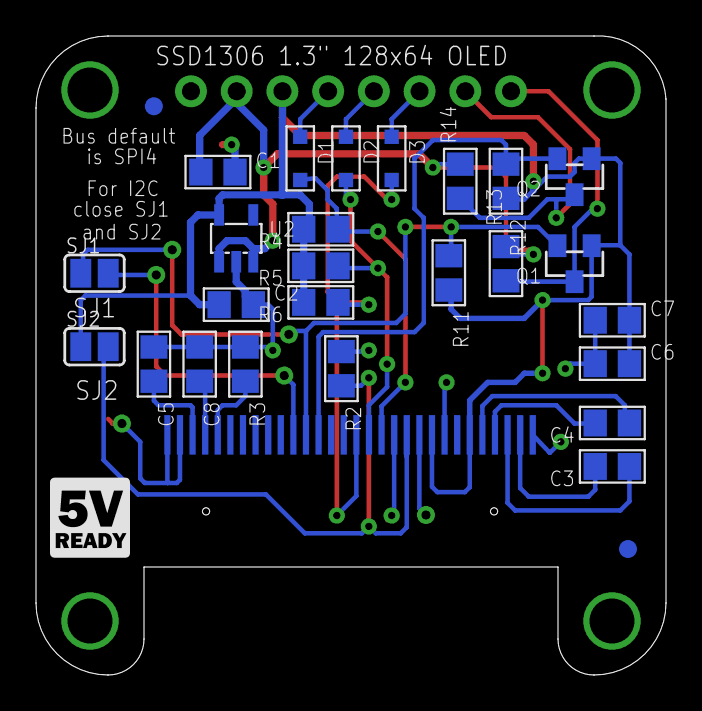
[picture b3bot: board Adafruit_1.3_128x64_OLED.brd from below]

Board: 2 copper layers, 35.0 x 35.5 mm, 35 parts (28 on the bottom side), 22 nets.

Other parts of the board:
U$27: ADAFRUIT_2.5MM
U$28: LOGIC_5VREADY_5MM

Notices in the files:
parts and their libraries:
SparkFun-Switches: Licensing: Creative Commons ShareAlike 4.0 International - https://creativecommons.org/licenses/by-sa/4.0
SparkFun-Aesthetics: Released under the Creative Commons Attribution Share-Alike 4.0 License
SparkFun-Aesthetics: https://creativecommons.org/licenses/by-sa/4.0
